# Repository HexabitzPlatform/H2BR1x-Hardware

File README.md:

# H2BR1x-Hardware
Hexabitz Pulse Oximeter & Heart-Rate Sensor Module Hardware Design

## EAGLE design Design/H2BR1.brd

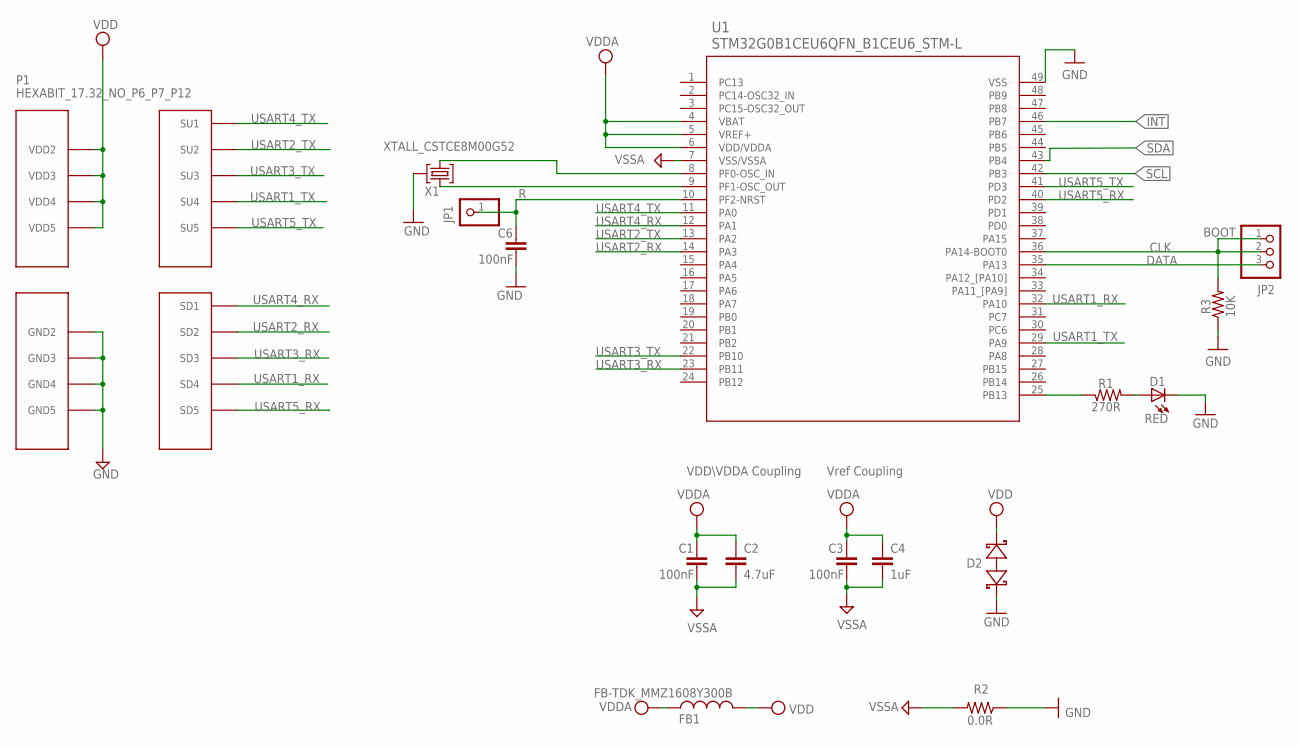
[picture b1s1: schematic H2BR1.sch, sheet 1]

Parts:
C1, C3, C6: 100nF; C-0603
C2: 4.7uF; C-0805
C4: 1uF; C-0805
D1: RED; VLMS1300-GS08; MPN VLMS1300-GS08
D2: BOURNS_CDSOD323-T03SCBOURNS_CDSOD323-T03SC_0_0; BOURNS_CDSOD323-T03SC_0
FB1: FB-TDK_MMZ1608Y300B; FB-0603; MPN MMZ1608Y300B
JP1: R; 1X01
JP2: PINHD-1X3; 1X03
P1: HEXABIT_17.32_NO_P6_P7_P12
R1: 270R; R-0603
R2: 0.0R; R-0603; MPN RC0603JR-070RL
R3: 10K; R-0603
TRIMBLE-LOGO1: HEXA-LOGO
U1: STM32G0B1CEU6QFN_B1CEU6_STM-L; QFN_B1CEU6_STM-L
X1: XTALL_CSTCE8M00G52

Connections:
CLK: JP2.1, JP2.2, R3.2, U1.36 (PA14-BOOT0)
DATA: JP2.3, U1.35 (PA13)
GND: C6.2, D1.C, D2.1 (A), P1.PAD_PD8 (GND2), P1.PAD_PD9 (GND3), P1.PAD_PD10 (GND4), P1.PAD_PD11 (GND5), R2.1, R3.1, U1.49 (VSS), X1.P$2 (2); also elsewhere on the board
INT: U1.46 (PB7); also elsewhere on the board
unnamed: R1.1, U1.25 (PB13)
unnamed: D1.A, R1.2
unnamed: C6.1, JP1.1, U1.10 (PF2-NRST)
unnamed: U1.9 (PF1-OSC_OUT), X1.P$1 (1)
unnamed: U1.8 (PF0-OSC_IN), X1.P$3 (3)
SCL: U1.42 (PB3); also elsewhere on the board
SDA: U1.43 (PB4); also elsewhere on the board
USART1_RX: P1.PAD_PD4 (SD4), U1.32 (PA10)
USART1_TX: P1.PAD_PU4 (SU4), U1.29 (PA9)
USART2_RX: P1.PAD_PD2 (SD2), U1.14 (PA3)
USART2_TX: P1.PAD_PU2 (SU2), U1.13 (PA2)
USART3_RX: P1.PAD_PD3 (SD3), U1.23 (PB11)
USART3_TX: P1.PAD_PU3 (SU3), U1.22 (PB10)
USART4_RX: P1.PAD_PD1 (SD1), U1.12 (PA1)
USART4_TX: P1.PAD_PU1 (SU1), U1.11 (PA0)
USART5_RX: P1.PAD_PD5 (SD5), U1.40 (PD2)
USART5_TX: P1.PAD_PU5 (SU5), U1.41 (PD3)
VDD: D2.2 (C), FB1.2, P1.PAD_PU8 (VDD2), P1.PAD_PU9 (VDD3), P1.PAD_PU10 (VDD4), P1.PAD_PU11 (VDD5); also elsewhere on the board
VDDA: C1.1, C2.1, C3.1, C4.1, FB1.1, U1.4 (VBAT), U1.5 (VREF+), U1.6 (VDD/VDDA)
VSSA: C1.2, C2.2, C3.2, C4.2, R2.2, U1.7 (VSS/VSSA)

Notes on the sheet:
Vref Coupling
VDD\VDDA Coupling
BOOT

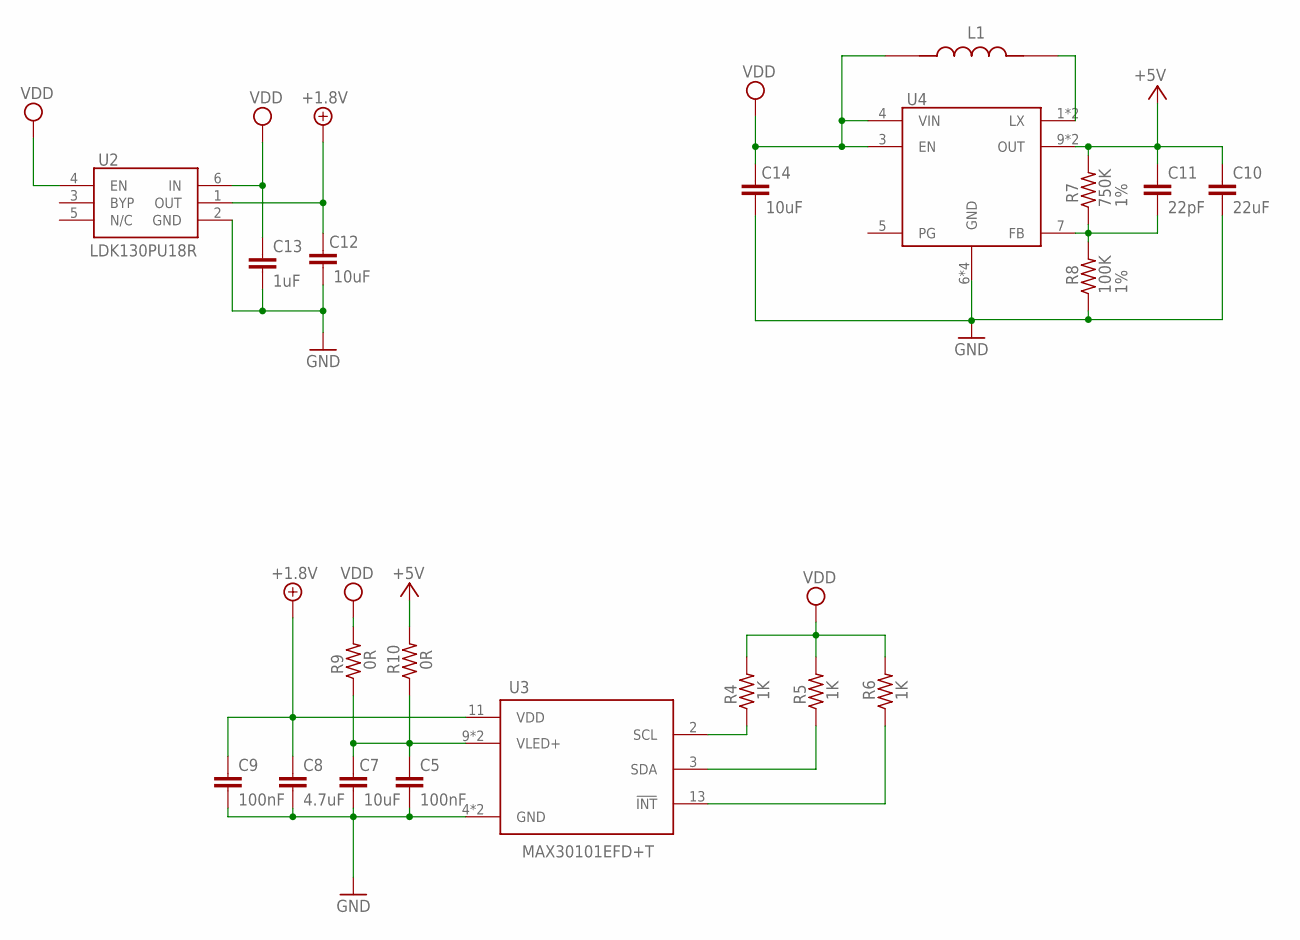
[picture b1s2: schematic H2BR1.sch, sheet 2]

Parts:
C5, C9: 100nF; C-0603
C7, C12, C14: 10uF; C-0805
C8: 4.7uF; C-0805
C10: 22uF; C-0603
C11: 22pF; C-0603
C13: 1uF; C-0805
L1: ASMPH08062R2MT; INDC1608X95N; MPN ASMPH-0806-2R2M-T
R4, R5, R6: 1K; R-0603
R7: 750K; R-0603; TOLERANCE 1%
R8: 100K; R-0603; TOLERANCE 1%
R9, R10: 0R; R-0603
U2: LDK130PU18R
U3: MAX30101EFD+T; 14-LEAD-OESIP
U4: PAM2401YPADJ; SON45P300X300X63-13N

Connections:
+1.8V: C8.1, C9.1, C12.1, U2.1 (OUT), U3.11 (VDD)
+5V: C10.1, C11.1, R7.2, R10.2, U4.9 (OUT), U4.10 (OUT)
GND: C5.2, C7.2, C8.2, C9.2, C10.2, C12.2, C13.2, C14.2, R8.1, U2.2 (GND), U3.4 (GND), U3.12 (GND), U4.6 (GND), U4.11 (GND), U4.12 (GND), U4.13 (GND); also elsewhere on the board
INT: R6.1, U3.13 (!INT); also elsewhere on the board
unnamed: C5.1, C7.1, R9.1, R10.1, U3.9 (VLED+), U3.10 (VLED+)
unnamed: C11.2, R7.1, R8.2, U4.7 (FB)
unnamed: L1.2, U4.1 (LX), U4.2 (LX)
SCL: R4.1, U3.2 (SCL); also elsewhere on the board
SDA: R5.1, U3.3 (SDA); also elsewhere on the board
VDD: C13.1, C14.1, L1.1, R4.2, R5.2, R6.2, R9.2, U2.4 (EN), U2.6 (IN), U4.3 (EN), U4.4 (VIN); also elsewhere on the board

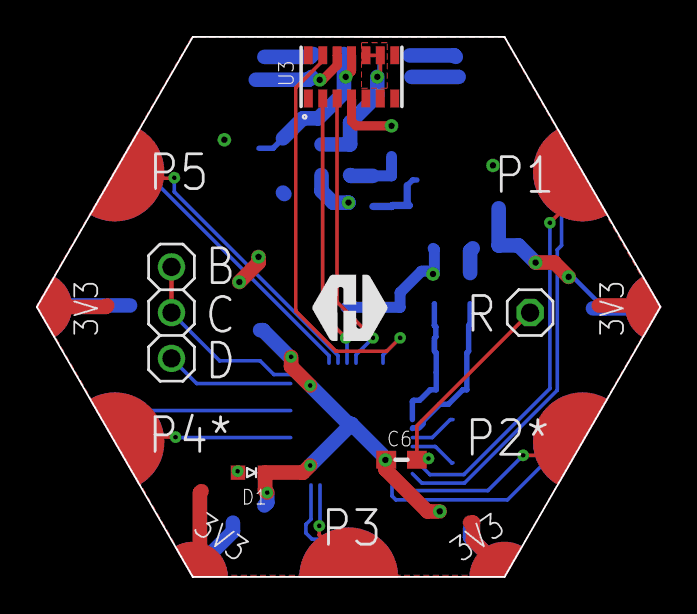
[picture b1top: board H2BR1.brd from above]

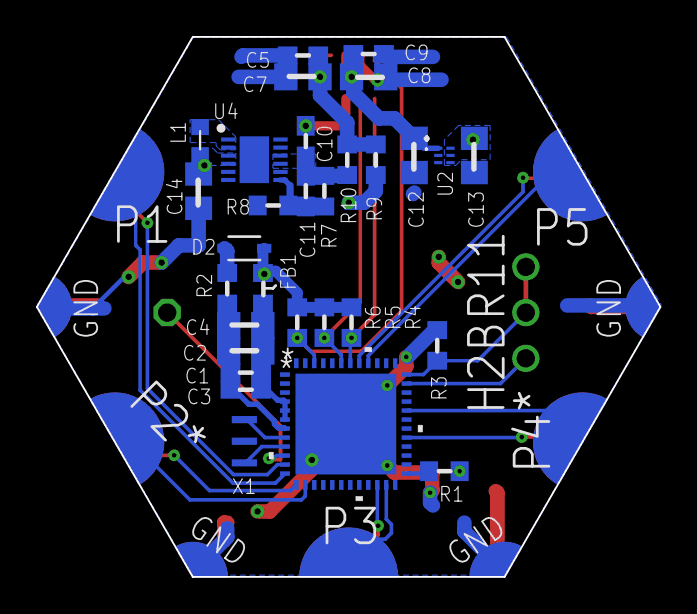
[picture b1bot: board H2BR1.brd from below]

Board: 2 copper layers, 34.6 x 30.0 mm, 37 parts (30 on the bottom side), 29 nets.

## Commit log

2022-08-19 Added .gitignore file
2022-08-23 no message
2022-08-24 Edit Readme file
2023-02-15 -Correcting some documentaion issues
2024-12-25 -The final design, all done.
2025-01-14 Resolve the issue with the silkscreen layer.

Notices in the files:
parts and their libraries:
COPYRIGHT: Copyright (C) 2021 Ultra Librarian. All rights reserved.
